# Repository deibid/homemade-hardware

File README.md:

# homemade-hardware
Repo containing EAGLE, Arduino and other electronics files for the homemade hardware course at NYU ITP

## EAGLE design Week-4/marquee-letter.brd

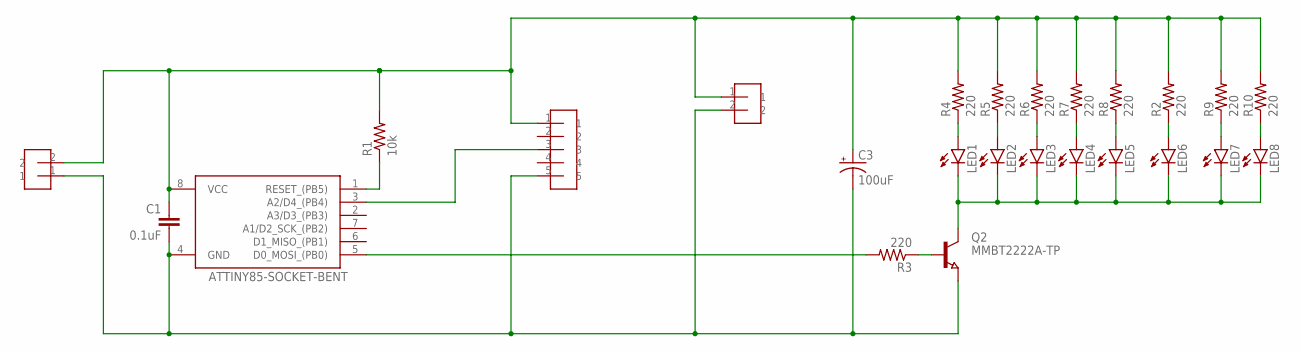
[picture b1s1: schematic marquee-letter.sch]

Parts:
C1: 0.1uF; 0805
C3: 100uF; PANASONIC_D
LED1, LED2, LED3, LED4, LED5, LED6, LED7, LED8: LED0603; LED-0603
POTENTIOMETER: HEADER-5
Q2: MMBT2222A-TP; SOT23
R1: 10k; 0805
R2, R4, R5, R6, R7, R8, R9, R10: 220; 0603-RES
R3: 220; 0805
U$1: ATTINY85-SOCKET-BENT; SOCKET-8PIN-BENT
U$2, U$3: HEADER-2

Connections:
5V: C1.1, C3.+, POTENTIOMETER.1, R1.2, R2.2, R4.2, R5.2, R6.2, R7.2, R8.2, R9.2, R10.2, U$1.8 (VCC), U$2.2, U$3.1
GND: C1.2, C3.-, POTENTIOMETER.5, Q2.2 (E), U$1.4 (GND), U$2.1, U$3.2
unnamed: LED1.A, R4.1
unnamed: LED6.A, R2.1
unnamed: R3.2, U$1.5 (D0_MOSI_(PB0))
unnamed: Q2.1 (B), R3.1
unnamed: LED1.C, LED2.C, LED3.C, LED4.C, LED5.C, LED6.C, LED7.C, LED8.C, Q2.3 (C)
unnamed: LED2.A, R5.1
unnamed: LED3.A, R6.1
unnamed: LED4.A, R7.1
unnamed: LED5.A, R8.1
unnamed: R1.1, U$1.1 (RESET_(PB5))
unnamed: LED8.A, R10.1
unnamed: LED7.A, R9.1
SENSOR: POTENTIOMETER.3, U$1.3 (A2/D4_(PB4))

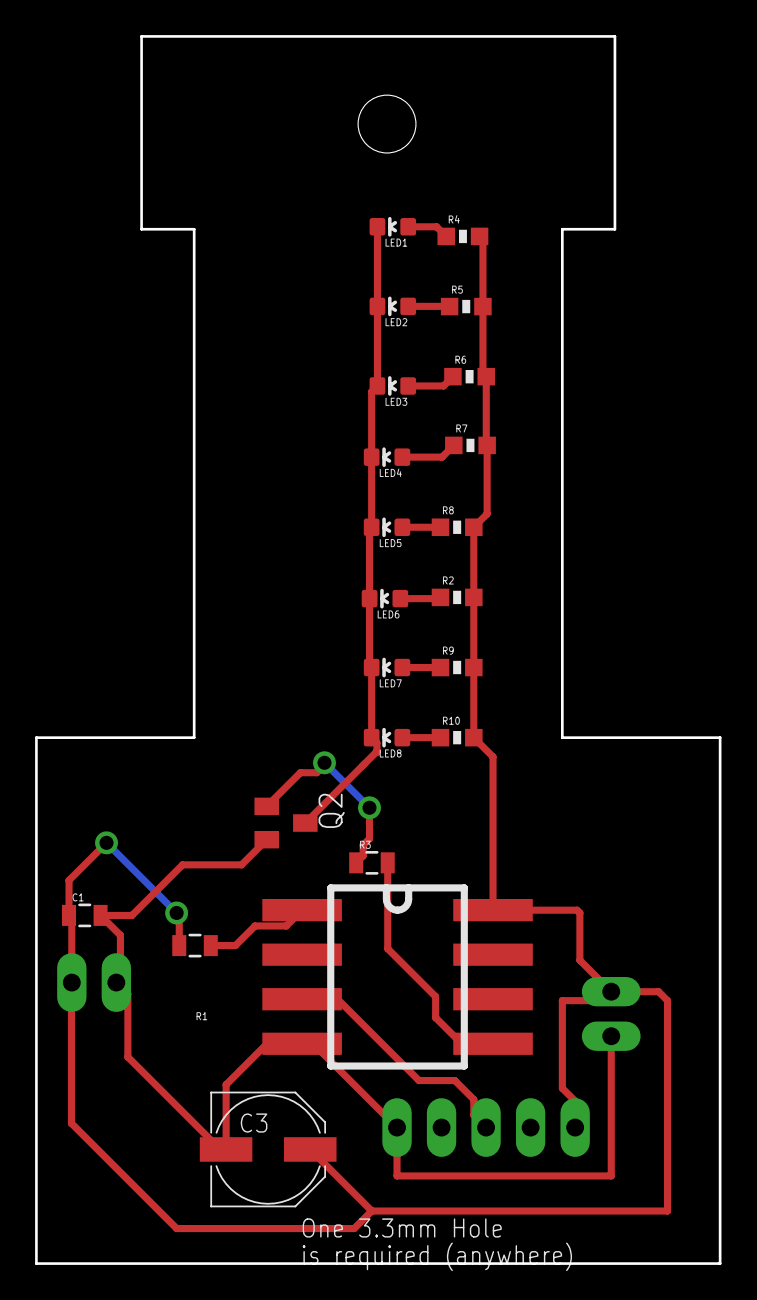
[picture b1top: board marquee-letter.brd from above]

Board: 2 copper layers, 39.0 x 70.0 mm, 25 parts (0 on the bottom side), 15 nets.

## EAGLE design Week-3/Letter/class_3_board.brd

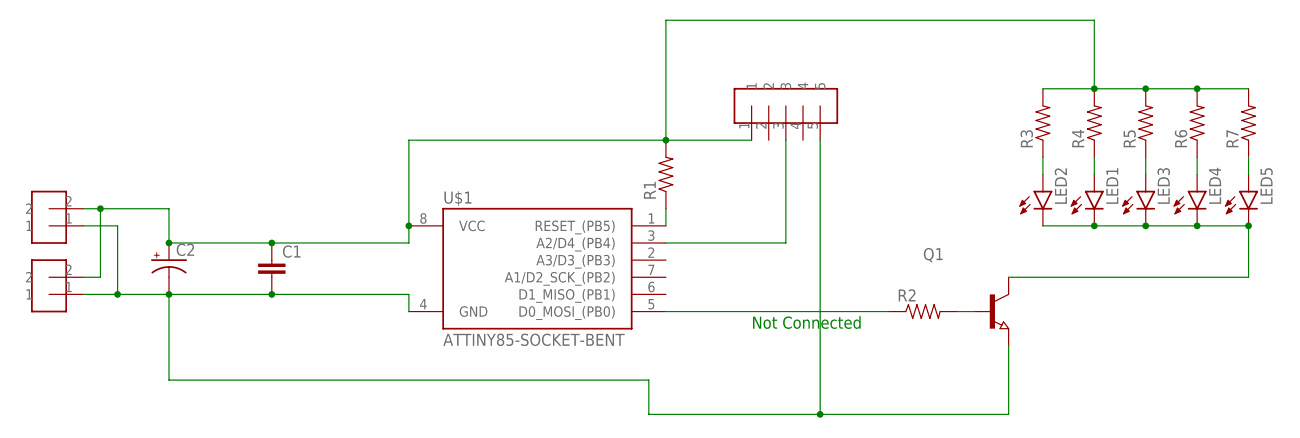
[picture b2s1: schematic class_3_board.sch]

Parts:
C1: CAP0603-CAP; 0603-CAP
C2: CAP_POLD; PANASONIC_D
LED1, LED2, LED3, LED4, LED5: LED0603; LED-0603
Q1: TRANSISTOR-NPN-SOT23; SOT23
R1, R2, R3, R4, R5, R6, R7: RESISTOR0603; 0603-RES
U$1: ATTINY85-SOCKET-BENT; SOCKET-8PIN-BENT
U$2: HEADER-5
U$3, U$4: HEADER-2

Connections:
unnamed: C1.1, C2.+, R1.2, R3.2, R4.2, R5.2, R6.2, R7.2, U$1.8 (VCC), U$2.1, U$3.2, U$4.2
unnamed: R1.1, U$1.1 (RESET_(PB5))
unnamed: C1.2, C2.-, Q1.2 (E), U$1.4 (GND), U$2.5, U$3.1, U$4.1
unnamed: R2.1, U$1.5 (D0_MOSI_(PB0))
unnamed: Q1.1 (B), R2.2
unnamed: U$1.3 (A2/D4_(PB4)), U$2.3
unnamed: LED2.A, R3.1
unnamed: LED4.A, R6.1
unnamed: LED5.A, R7.1
unnamed: LED3.A, R5.1
unnamed: LED1.A, R4.1
unnamed: LED1.C, LED2.C, LED3.C, LED4.C, LED5.C, Q1.3 (C)

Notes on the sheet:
Not Connected

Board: 2 copper layers, 19 parts (0 on the bottom side), 12 nets, no tracks yet.

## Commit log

2019-04-16 pushing previous work to repo
2019-04-16 pushing marquee letter demo and files
